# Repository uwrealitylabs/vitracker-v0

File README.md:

# vitracker-v0

## SOI JX-K06A-C1-M2 DVP/MIPI camera board made by Miles Milne

Features:
- DVP/i2c breakouts
- Raspberry pi compatible 2 lane MIPI port
- LED control via raspberry pi port

> [!CAUTION]
> This board has not been tested to function properly

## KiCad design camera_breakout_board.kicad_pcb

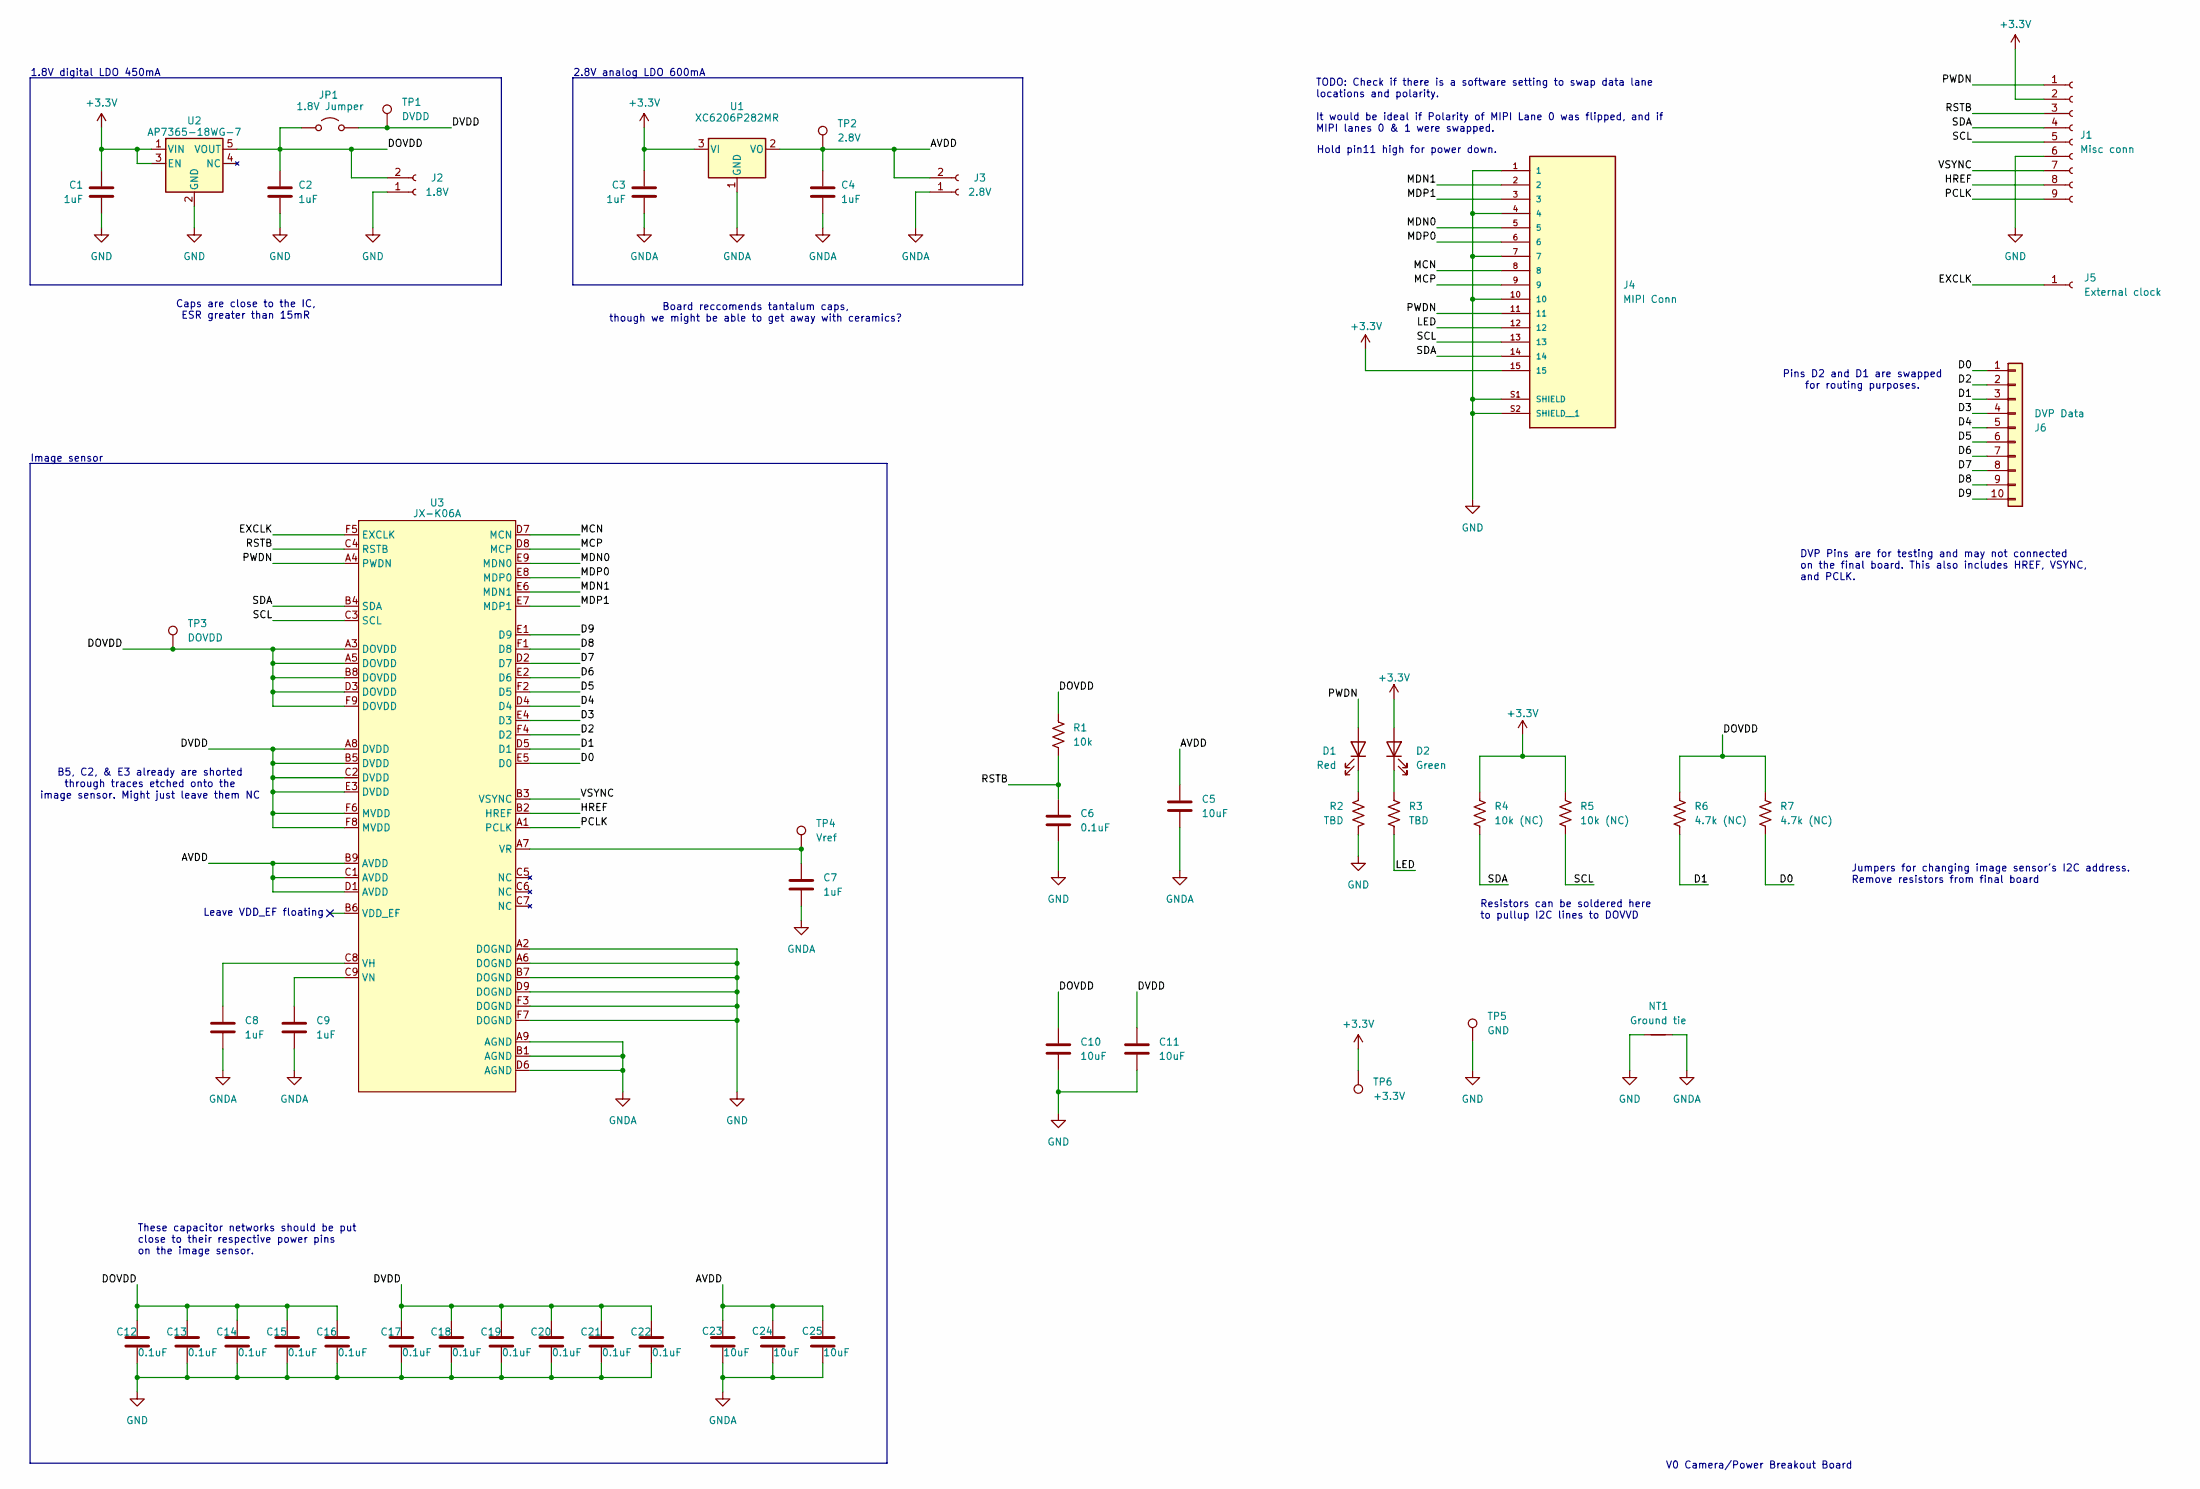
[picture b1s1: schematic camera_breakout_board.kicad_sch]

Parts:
C1, C2, C3, C4: 1uF; C_0402_1005Metric
C5, C10, C11, C23, C24, C25: 10uF; C_0402_1005Metric
C6, C12, C13, C14, C15, C16, C17, C18, C19, C20, C21, C22: 0.1uF; C_0402_1005Metric
C7, C8, C9: 1uF; C_0805_2012Metric_Pad1.18x1.45mm_HandSolder
D1: Red; LED_1206_3216Metric_Pad1.42x1.75mm_HandSolder
D2: Green; LED_1206_3216Metric_Pad1.42x1.75mm_HandSolder
J1: Misc conn; PinSocket_1x09_P2.54mm_Vertical
J2: 1.8V; PinSocket_1x02_P2.54mm_Vertical
J3: 2.8V; PinSocket_1x02_P2.54mm_Vertical
J4: MIPI Conn; AMPHENOL_SFW15R-2STE1LF; PARTREV AE
J5: External clock; PinSocket_1x01_P2.54mm_Vertical
J6: DVP Data; PinHeader_1x10_P2.54mm_Vertical
JP1: 1.8V Jumper; PinHeader_1x02_P2.54mm_Vertical
NT1: Ground tie; NetTie-2_SMD_Pad0.5mm
R1: 10k; R_0402_1005Metric
R2, R3: TBD; R_0805_2012Metric
R4, R5: 10k (NC); R_0805_2012Metric
R6, R7: 4.7k (NC); R_0805_2012Metric
TP1: DVDD; TestPoint_Pad_D1.0mm
TP2: 2.8V; TestPoint_Pad_D1.0mm
TP3: DOVDD; TestPoint_Pad_D1.0mm
TP4: Vref; TestPoint_Pad_D1.0mm
TP5: GND; TestPoint_Pad_D1.0mm
TP6: +3.3V; TestPoint_Pad_D1.0mm
U1: XC6206P282MR; SOT-23-3
U2: AP7365-18WG-7; SOT-23-5
U3: JX-K06A; WLCSP-51_L6.1-W4.1-P0.60-S0.55-TL

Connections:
+3.3V: C1.1, C3.1, D2.2 (A), J1.2, J4.15, R4.1, R5.1, TP6.1, U1.3 (VI), U2.1 (VIN), U2.3 (EN)
/AVDD: C4.1, C5.1, C23.1, C24.1, C25.1, J3.2, TP2.1, U1.2 (VO), U3.B9 (AVDD), U3.C1 (AVDD), U3.D1 (AVDD)
/D0: J6.1, R7.2, U3.E5 (D0)
/D1: J6.3, R6.2, U3.D5 (D1)
/D2: J6.2, U3.F4 (D2)
/D3: J6.4, U3.E4 (D3)
/D4: J6.5, U3.D4
/D5: J6.6, U3.F2 (D5)
/D6: J6.7, U3.E2 (D6)
/D7: J6.8, U3.D2 (D7)
/D8: J6.9, U3.F1 (D8)
/D9: J6.10, U3.E1 (D9)
/DOVDD: C2.1, C10.1, C12.1, C13.1, C14.1, C15.1, C16.1, J2.2, JP1.1 (A), R1.1, R6.1, R7.1, TP3.1, U2.5 (VOUT), U3.A3 (DOVDD), U3.A5 (DOVDD), U3.B8 (DOVDD), U3.D3 (DOVDD), U3.F9 (DOVDD)
/DVDD: C11.1, C17.1, C18.1, C19.1, C20.1, C21.1, C22.1, JP1.2 (B), TP1.1, U3.A8 (DVDD), U3.B5 (DVDD), U3.C2 (DVDD), U3.E3 (DVDD), U3.F6 (MVDD), U3.F8 (MVDD); also elsewhere on the board
/EXCLK: J5.1, U3.F5 (EXCLK)
/HREF: J1.8, U3.B2 (HREF)
/LED: J4.12, R3.2
/MCN: J4.8, U3.D7 (MCN)
/MCP: J4.9, U3.D8 (MCP)
/MDN0: J4.5, U3.E9 (MDN0)
/MDN1: J4.2, U3.E6 (MDN1)
/MDP0: J4.6, U3.E8 (MDP0)
/MDP1: J4.3, U3.E7 (MDP1)
/PCLK: J1.9, U3.A1 (PCLK)
/PWDN: D1.2 (A), J1.1, J4.11, U3.A4 (PWDN)
/RSTB: C6.1, J1.3, R1.2, U3.C4 (RSTB)
/SCL: J1.5, J4.13, R5.2, U3.C3 (SCL)
/SDA: J1.4, J4.14, R4.2, U3.B4 (SDA)
/VSYNC: J1.7, U3.B3 (VSYNC)
GND: C1.2, C2.2, C6.2, C10.2, C11.2, C12.2, C13.2, C14.2, C15.2, C16.2, C17.2, C18.2, C19.2, C20.2, C21.2, C22.2, J1.6, J2.1, J4.1, J4.4, J4.7, J4.10, J4.S1 (SHIELD), J4.S2 (SHIELD__1), NT1.1, R2.2, TP5.1, U2.2 (GND), U3.A2 (DOGND), U3.A6 (DOGND), U3.B7 (DOGND), U3.D9 (DOGND), U3.F3 (DOGND), U3.F7 (DOGND)
GNDA: C3.2, C4.2, C5.2, C7.2, C8.2, C9.2, C23.2, C24.2, C25.2, J3.1, NT1.2, U1.1 (GND), U3.A9 (AGND), U3.B1 (AGND), U3.D6 (AGND)
unnamed: D1.1 (K), R2.1
unnamed: D2.1 (K), R3.1
unnamed: C8.1, U3.C8 (VH)
unnamed: C9.1, U3.C9 (VN)
unnamed: C7.1, TP4.1, U3.A7 (VR)

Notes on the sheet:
1.8V digital LDO 450mA
Pins D2 and D1 are swapped for routing purposes.
V0 Camera/Power Breakout Board
Hold pin11 high for power down.
Resistors can be soldered here to pullup I2C lines to DOVVD
TODO: Check if there is a software setting to swap data lane locations and polarity. It would be ideal if Polarity of MIPI Lane 0 was flipped, and if MIPI lanes 0 & 1 were swapped.
These capacitor networks should be put close to their respective power pins on the image sensor.
B5, C2, & E3 already are shorted through traces etched onto the image sensor. Might just leave them NC
2.8V analog LDO 600mA
Image sensor
DVP Pins are for testing and may not connected on the final board. This also includes HREF, VSYNC, and PCLK.
Board reccomends tantalum caps, though we might be able to get away with ceramics?
Leave VDD_EF floating
Caps are close to the IC, ESR greater than 15mR
Jumpers for changing image sensor's I2C address. Remove resistors from final board

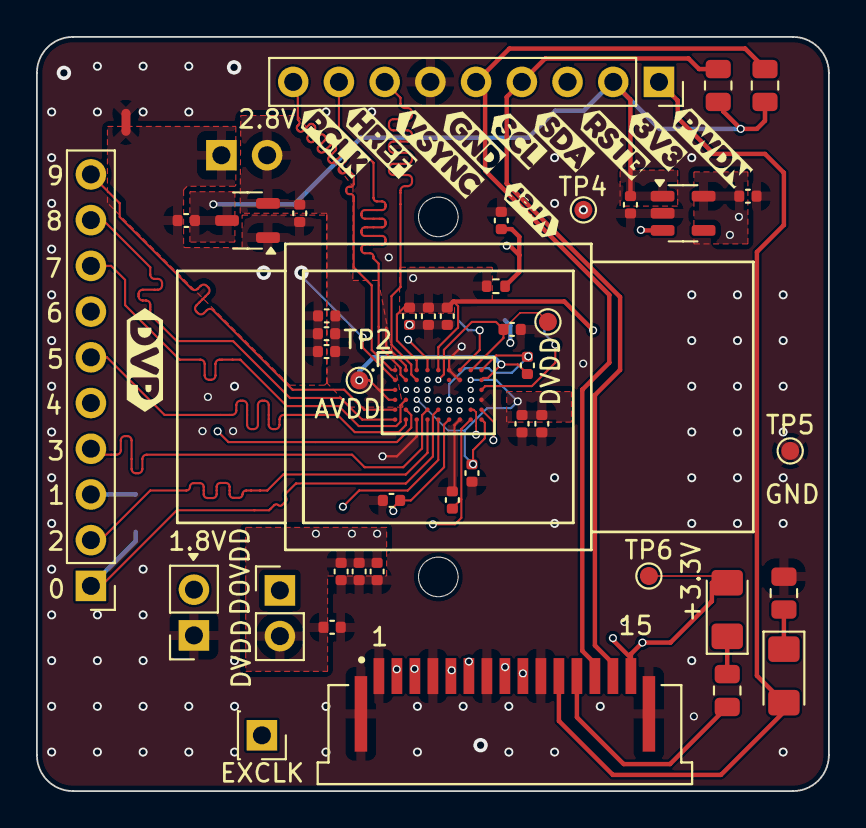
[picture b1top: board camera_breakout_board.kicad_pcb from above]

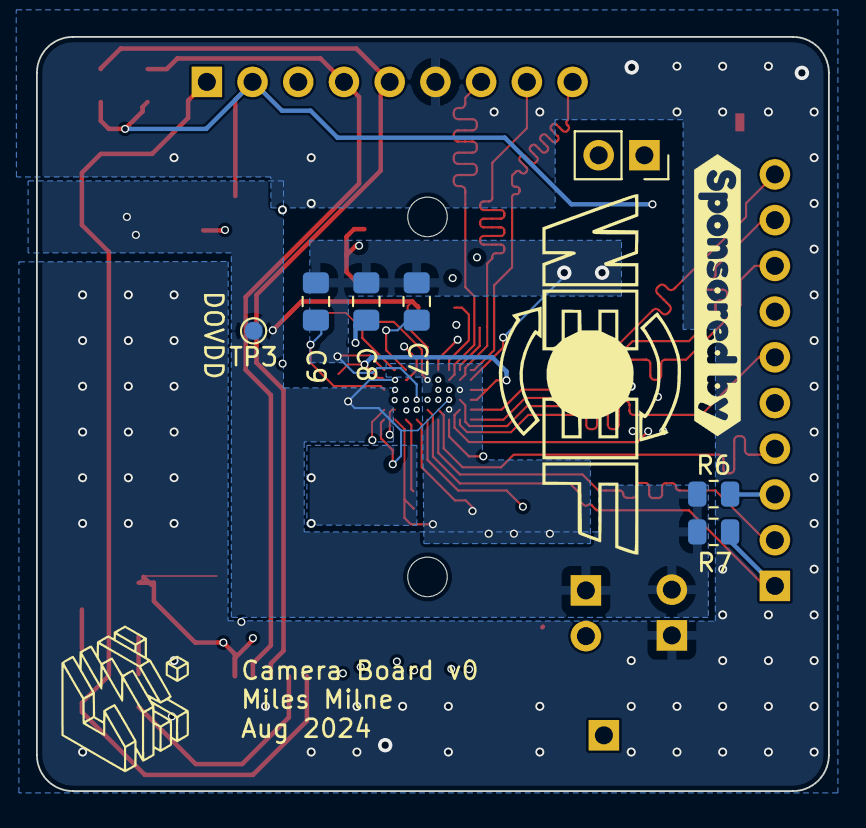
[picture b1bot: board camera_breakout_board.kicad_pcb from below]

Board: 6 copper layers, 44.0 x 41.9 mm, 63 parts (8 on the bottom side), 36 nets.

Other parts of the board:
DVDD: DVDD; TestPoint_Pad_D1.0mm
kibuzzard-66C7B8BC: G***; kibuzzard-66C7B8BC
kibuzzard-66C7B86B: G***; kibuzzard-66C7B86B
kibuzzard-66C654AF: G***; kibuzzard-66C654AF
kibuzzard-66C654D1: G***; kibuzzard-66C654D1
kibuzzard-66C6556F: G***; kibuzzard-66C6556F
kibuzzard-66C65292: G***; kibuzzard-66C65292
kibuzzard-66C65548: G***; kibuzzard-66C65548
kibuzzard-66C65550: G***; kibuzzard-66C65550
kibuzzard-66C65558: G***; kibuzzard-66C65558
kibuzzard-66C65564: G***; kibuzzard-66C65564
kibuzzard-66C65576: G***; kibuzzard-66C65576
kibuzzard-66C65581: G***; kibuzzard-66C65581

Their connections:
/DVDD: DVDD.1; also elsewhere on the board

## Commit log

2024-08-27 isolated project with updated readme
